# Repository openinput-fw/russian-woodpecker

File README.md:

# russian-woodpecker

*russian-woodpecker* is a usb HS (capable of 8kHz polling rate) 2.4GHz radio receiver dongle for use with input devices.

Please see the [documentation](https://russian-woodpecker.readthedocs.io/en/latest)
for more information.

## Specifications
- 8 kHz polling rate suppor
- 2.4GHz radio
- smol, but not that smol

## License

This hardware is licensed under the [CERN-OHL-P v2](LICENSE) license.

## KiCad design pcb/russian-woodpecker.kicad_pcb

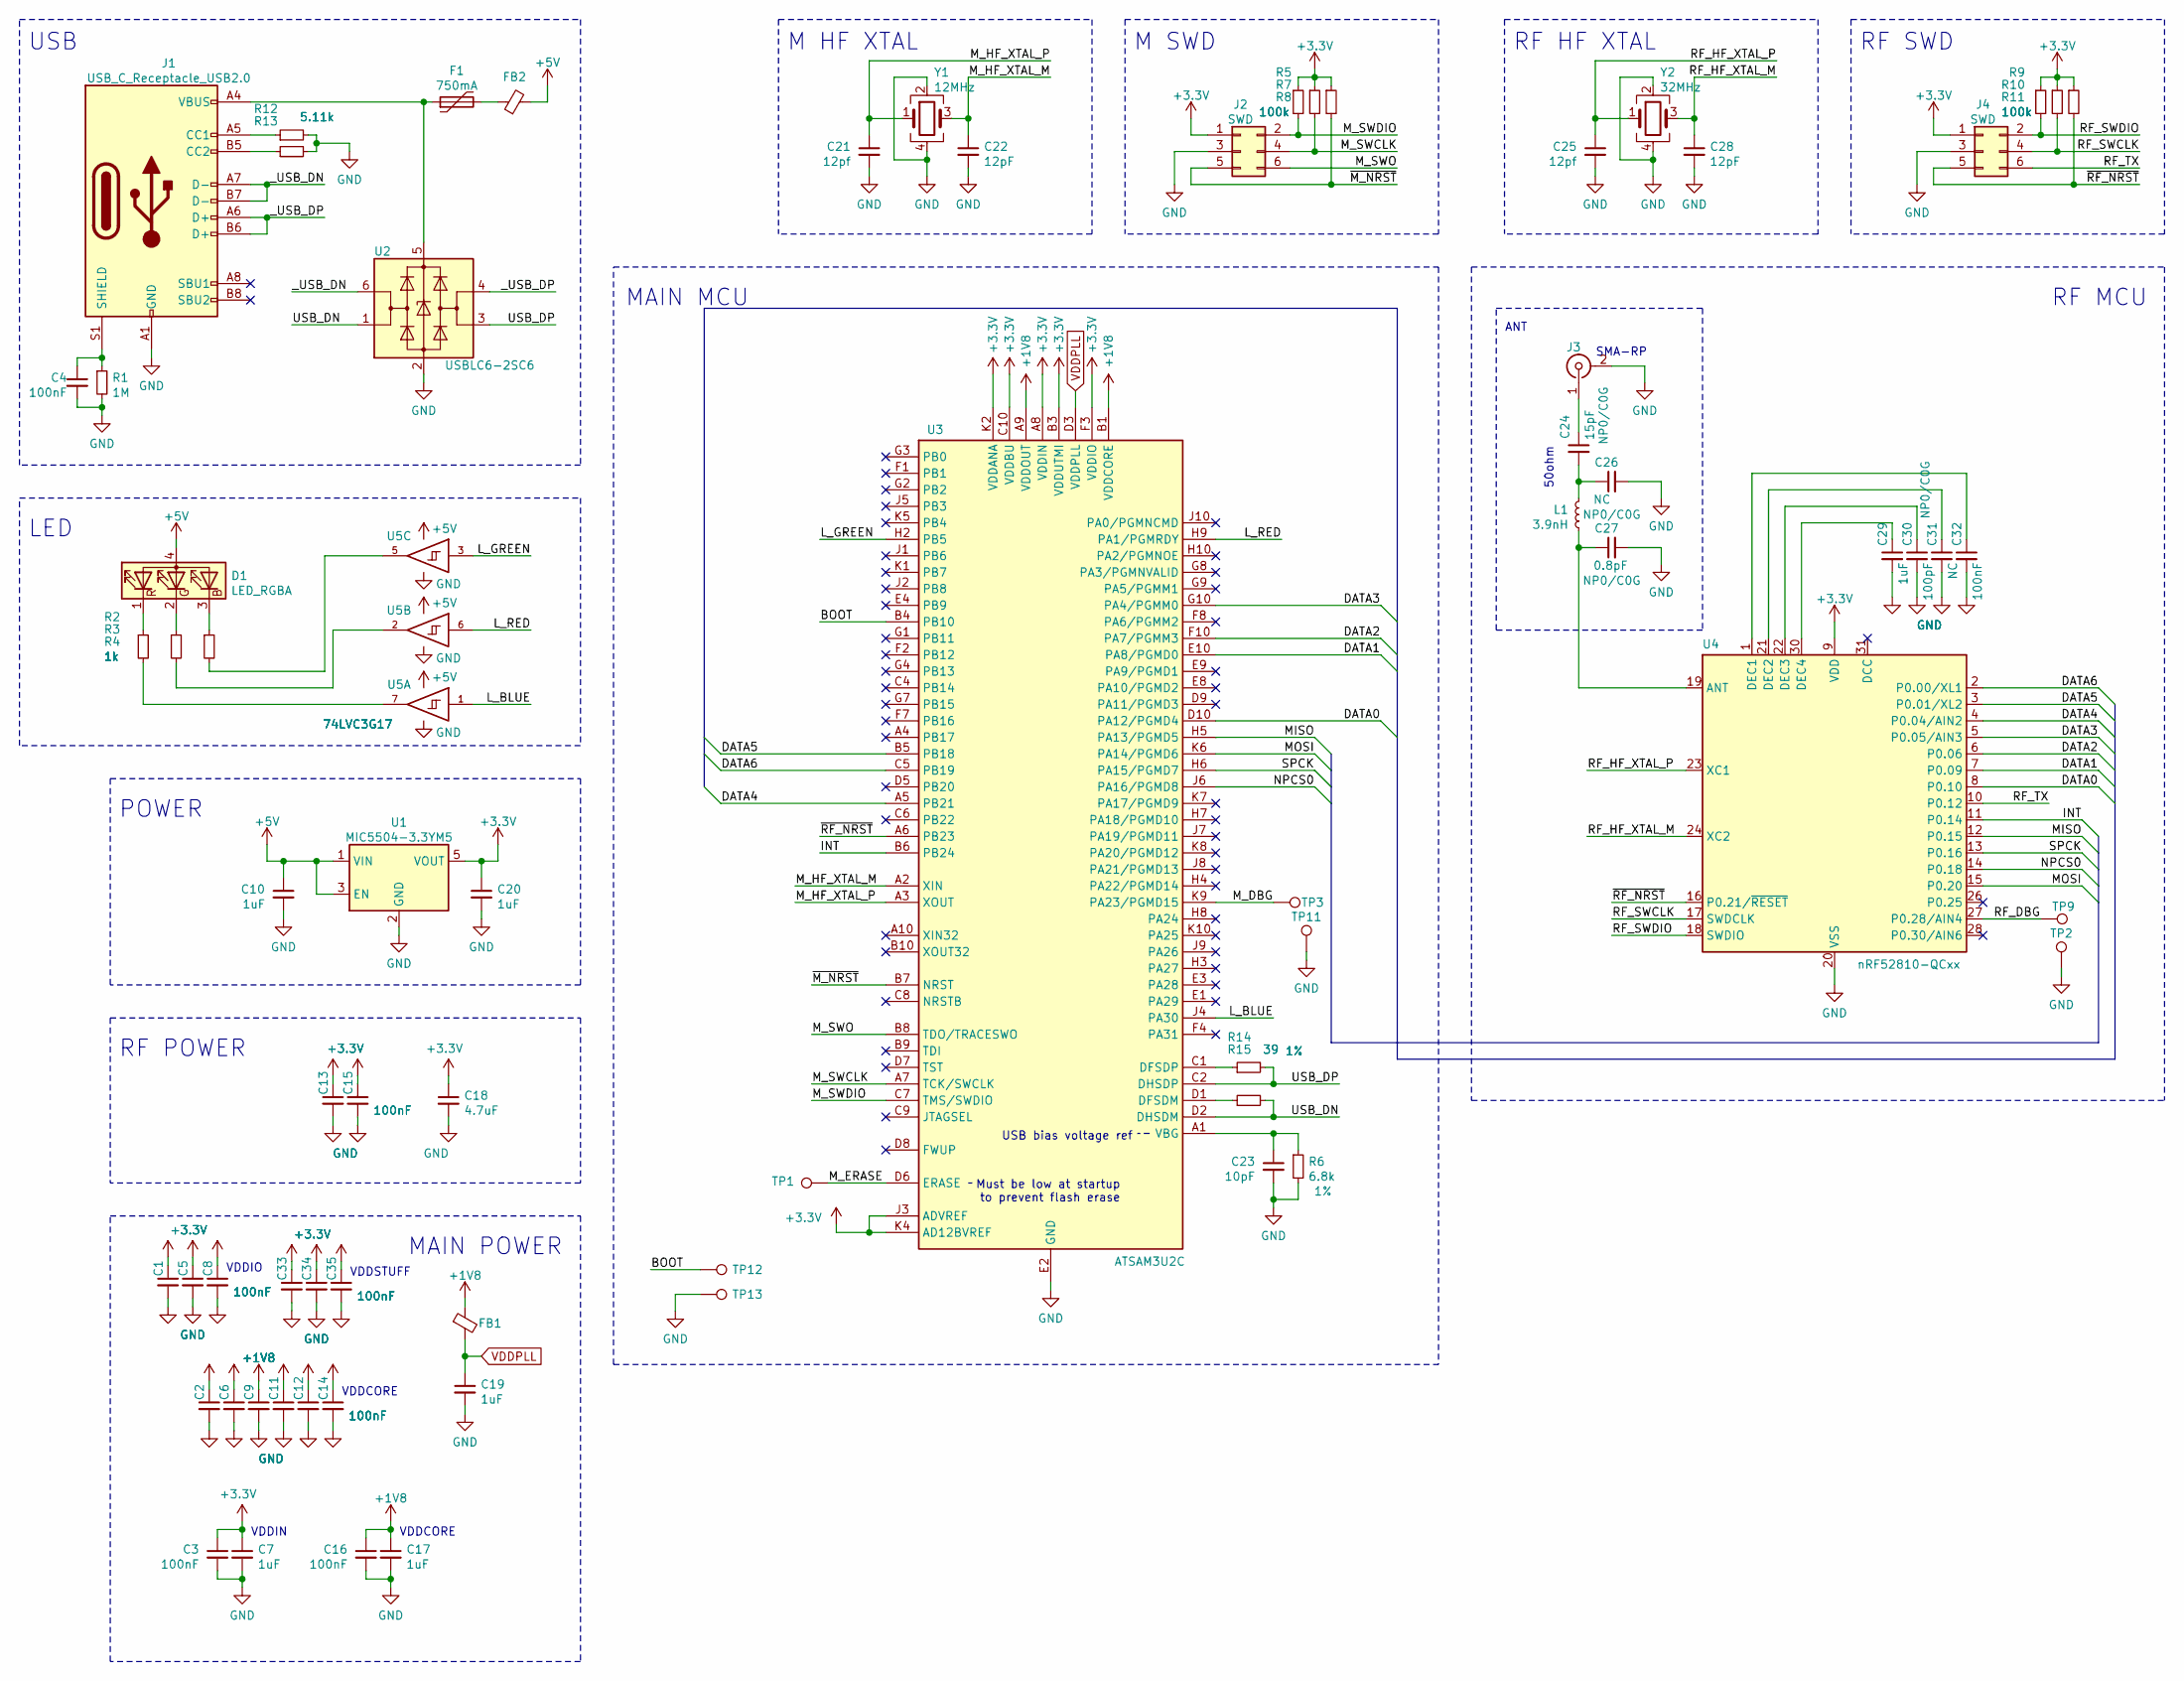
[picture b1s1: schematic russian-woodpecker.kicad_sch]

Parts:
C1, C2, C3, C4, C5, C6, C8, C9, C11, C12, C13, C14, C15, C16, C32, C33, C34, C35: 100nF; C_0402_1005Metric
C7, C10, C17, C19, C20, C29: 1uF; C_0402_1005Metric
C18: 4.7uF; C_0603_1608Metric
C21, C25: 12pf; C_0402_1005Metric
C22, C28: 12pF; C_0402_1005Metric
C23: 10pF; C_0402_1005Metric
C24: 15pF; C_0402_1005Metric
C26, C31: NC; C_0402_1005Metric
C27: 0.8pF; C_0402_1005Metric
C30: 100pF; C_0402_1005Metric
D1: LED_RGBA; LED_LiteOn_LTST-C19HE1WT
F1: 750mA; Fuse_0603_1608Metric
FB1, FB2: L_0402_1005Metric
J1: USB_C_Receptacle_USB2.0; USB_C_Receptacle_HRO_TYPE-C-31-M-12
J2, J4: SWD; Tag-Connect_TC2030-IDC-NL_2x03_P1.27mm_Vertical
J3: SMA-RP; SMA_Amphenol_132289_EdgeMount
L1: 3.9nH; L_0402_1005Metric
R1: 1M; R_0402_1005Metric
R2, R3, R4: 1k; R_0402_1005Metric
R5, R7, R8, R9, R10, R11: 100k; R_0402_1005Metric
R6: 6.8k; R_0402_1005Metric; Tolerance 1%
R12, R13: 5.11k; R_0402_1005Metric
R14, R15: 39; R_0402_1005Metric; Tolerance 1%
TP1, TP2, TP3, TP9, TP11, TP12, TP13: TestPoint_Pad_D1.0mm
U1: MIC5504-3.3YM5; SOT-23-5
U2: USBLC6-2SC6; SOT-23-6
U3: ATSAM3U2C; TFBGA-100_9.0x9.0mm_Layout10x10_P0.8mm
U4: nRF52810-QCxx; QFN-32-1EP_5x5mm_P0.5mm_EP3.6x3.6mm
U5: 74LVC3G17; VSSOP-8_2.3x2mm_P0.5mm
Y1: 12MHz; Crystal_SMD_3225-4Pin_3.2x2.5mm
Y2: 32MHz; Crystal_SMD_3225-4Pin_3.2x2.5mm

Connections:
+1V8: C2.1, C6.1, C9.1, C11.1, C12.1, C14.1, C16.1, C17.1, FB1.1, U3.A9 (VDDOUT), U3.B1 (VDDCORE), U3.D4 (VDDCORE), U3.E7 (VDDCORE), U3.F9 (VDDCORE), U3.G5 (VDDCORE), U3.H1 (VDDCORE)
+3V3: C1.1, C3.1, C5.1, C7.1, C8.1, C13.1, C15.1, C18.1, C20.1, C33.1, C34.1, C35.1, J2.1, J4.1, R5.1, R7.1, R8.1, R9.1, R10.1, R11.1, U1.5 (VOUT), U3.A8 (VDDIN), U3.B3 (VDDUTMI), U3.C10 (VDDBU), U3.E6 (VDDIO), U3.F3 (VDDIO), U3.F5 (VDDIO), U3.J3 (ADVREF), U3.K2 (VDDANA), U3.K4 (AD12BVREF), U4.9 (VDD), U4.25 (VDD), U4.32 (VDD)
+5V: C10.1, D1.4 (A), FB2.2, U1.1 (VIN), U1.3 (EN), U5.8 (VCC)
/BOOT: TP12.1, U3.B4 (PB10)
/DATA0: U3.D10 (PA12/PGMD4), U4.8 (P0.10)
/DATA1: U3.E10 (PA8/PGMD0), U4.7 (P0.09)
/DATA2: U3.F10 (PA7/PGMM3), U4.6 (P0.06)
/DATA3: U3.G10 (PA4/PGMM0), U4.5 (P0.05/AIN3)
/DATA4: U3.A5 (PB21), U4.4 (P0.04/AIN2)
/DATA5: U3.B5 (PB18), U4.3 (P0.01/XL2)
/DATA6: U3.C5 (PB19), U4.2 (P0.00/XL1)
/INT: U3.B6 (PB24), U4.11 (P0.14)
/L_BLUE: U3.J4 (PA30), U5.1
/L_GREEN: U3.H2 (PB5), U5.3
/L_RED: U3.H9 (PA1/PGMRDY), U5.6
/MISO: U3.H5 (PA13/PGMD5), U4.12 (P0.15)
/MOSI: U3.K6 (PA14/PGMD6), U4.15 (P0.20)
/M_DBG: TP3.1, U3.K9 (PA23/PGMD15)
/M_ERASE: TP1.1, U3.D6 (ERASE)
/M_HF_XTAL_M: C22.1, U3.A2 (XIN), Y1.3
/M_HF_XTAL_P: C21.1, U3.A3 (XOUT), Y1.1
/M_SWCLK: J2.4, R7.2, U3.A7 (TCK/SWCLK)
/M_SWDIO: J2.2, R5.2, U3.C7 (TMS/SWDIO)
/M_SWO: J2.6, U3.B8 (TDO/TRACESWO)
/NPCS0: U3.J6 (PA16/PGMD8), U4.14 (P0.18)
/RF_DBG: TP9.1, U4.27 (P0.28/AIN4)
/RF_HF_XTAL_M: C28.1, U4.24 (XC2), Y2.3
/RF_HF_XTAL_P: C25.1, U4.23 (XC1), Y2.1
/RF_SWCLK: J4.4, R10.2, U4.17 (SWDCLK)
/RF_SWDIO: J4.2, R9.2, U4.18 (SWDIO)
/RF_TX: J4.6, U4.10 (P0.12)
/SPCK: U3.H6 (PA15/PGMD7), U4.13 (P0.16)
/USB_DN: R15.2, U2.1 (I/O1), U3.D2 (DHSDM)
/USB_DP: R14.2, U2.3 (I/O2), U3.C2 (DHSDP)
/_USB_DN: J1.A7 (D-), J1.B7 (D-), U2.6 (I/O1)
/_USB_DP: J1.A6 (D+), J1.B6 (D+), U2.4 (I/O2)
/~M_NRST: J2.5, R8.2, U3.B7 (NRST)
/~RF_NRST: J4.5, R11.2, U3.A6 (PB23), U4.16 (P0.21/~RESET)
GND: C1.2, C2.2, C3.2, C4.2, C5.2, C6.2, C7.2, C8.2, C9.2, C10.2, C11.2, C12.2, C13.2, C14.2, C15.2, C16.2, C17.2, C18.2, C19.2, C20.2, C21.2, C22.2, C23.2, C25.2, C26.2, C27.2, C28.2, C29.2, C30.2, C31.2, C32.2, C33.2, C34.2, C35.2, J1.A1 (GND), J1.A12 (GND), J1.B1 (GND), J1.B12 (GND), J2.3, J3.2 (Ext), J4.3, R1.2, R6.2, R12.2, R13.2, TP2.1, TP11.1, TP13.1, U1.2 (GND), U2.2 (GND), U3.B2 (GNDUTMI), U3.C3 (GNDPLL), U3.E2 (GND), U3.E5 (GNDBU), U3.F6 (GND), U3.G6 (GND), U3.K3 (GNDANA), U4.20 (VSS), U4.29 (VSS), U4.33 (VSS), U5.4 (GND), Y1.2, Y1.4, Y2.2, Y2.4
unnamed: C4.1, J1.S1 (SHIELD), R1.1
unnamed: C23.1, R6.1, U3.A1 (VBG)
unnamed: C24.1, J3.1 (In)
unnamed: C24.2, C26.1, L1.2
unnamed: C27.1, L1.1, U4.19 (ANT)
unnamed: C29.1, U4.30 (DEC4)
unnamed: C30.1, U4.22 (DEC3)
unnamed: C31.1, U4.21 (DEC2)
unnamed: C32.1, U4.1 (DEC1)
unnamed: F1.1, J1.A4 (VBUS), J1.A9 (VBUS), J1.B4 (VBUS), J1.B9 (VBUS), U2.5 (VBUS)
unnamed: F1.2, FB2.1
unnamed: J1.A5 (CC1), R12.1
unnamed: J1.B5 (CC2), R13.1
unnamed: D1.1 (RK), R2.1
unnamed: R2.2, U5.7
unnamed: D1.2 (GK), R3.1
unnamed: R3.2, U5.2
unnamed: D1.3 (BK), R4.1
unnamed: R4.2, U5.5
unnamed: R14.1, U3.C1 (DFSDP)
unnamed: R15.1, U3.D1 (DFSDM)
VDDPLL: C19.1, FB1.2, U3.D3 (VDDPLL)

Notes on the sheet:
RF POWER
RF MCU
VDDIO
USB bias voltage ref
Must be low at startup to prevent flash erase
VDDCORE
USB
M SWD
RF HF XTAL
MAIN POWER
VDDSTUFF
VDDIN
RF SWD
LED
MAIN MCU
SMA-RP
M HF XTAL
POWER
ANT
50ohm

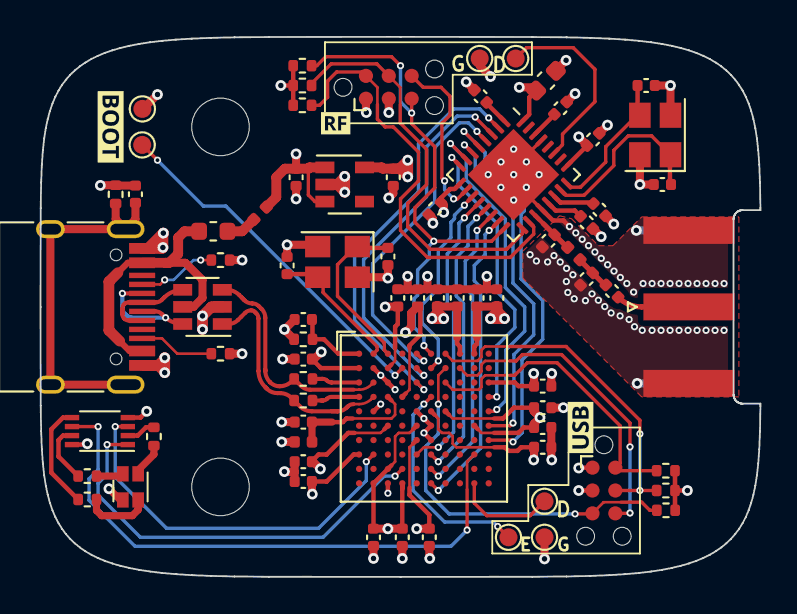
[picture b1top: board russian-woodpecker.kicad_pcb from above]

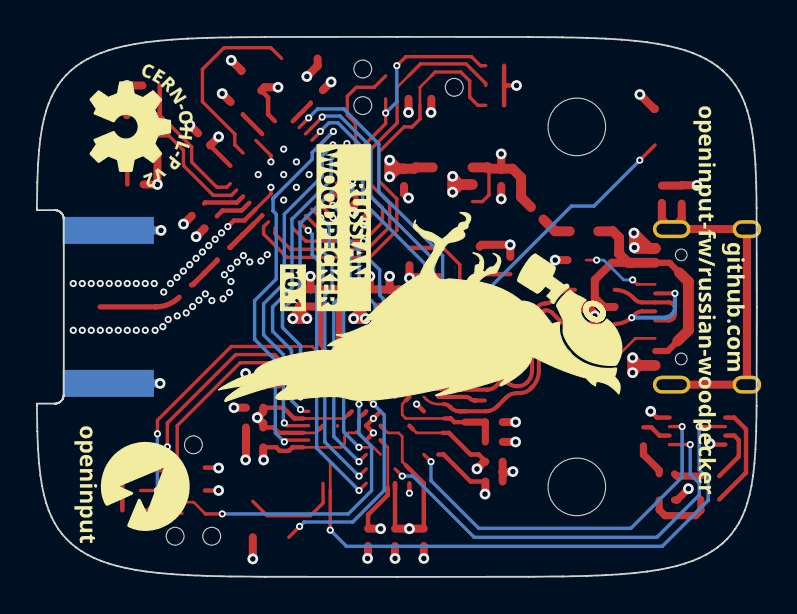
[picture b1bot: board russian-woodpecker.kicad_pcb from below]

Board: 4 copper layers, 40.0 x 30.0 mm, 82 parts (4 on the bottom side), 61 nets.

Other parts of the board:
MH0, MH0#2: MountingHole_3.2mm_M3
svg2mod, svg2mod#2, svg2mod#3, svg2mod#4, svg2mod#5, svg2mod#6, svg2mod#7: G***; svg2mod

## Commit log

2021-05-25 kicad: create kicad project
2021-05-26 kicad: add atsam3u lib
2021-05-26 sch: rev 0.1
2021-05-29 kicad: add SMA connector models
2021-05-29 cad: add dxf outline (superellipsoid genned in openscad)
2021-05-29 gitignore: kicad: add bakup entry in gitignore
2021-05-29 pcb: add boot button, change usb to type C, initial board
2021-05-29 readme: add board view
2021-05-29 asset: add woodpecker 'logo'
2021-06-05 pcb: finalize routing
2021-06-08 repo: update references in preparation for transfer to openinput org
2021-06-08 pcbnew: fix 3d model references
2021-06-08 readme: add oi logo, update board view
2021-06-08 assets: remove unused board view for r0.0
2021-06-08 kicad pro: update drc preferences
2021-06-09 pcb: change led drive circuitry
2021-10-15 assets: oi logo cleanup
2021-11-22 assets: move assets inside docs
2021-11-22 docs: add initial readthedocs documentation
2021-11-22 readme: remove documentation that is now on readthedocs
2021-11-22 docs: update index
2021-11-22 docs: move firmware info from readme to docs
2021-11-23 docs: add link to source
2021-12-15 readme: formating
2022-01-07 kicad: save pcb with v6.0

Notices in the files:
pcb/russian-woodpecker.kicad_pcb:
This source describes Open Hardware and is licensed under the CERN-OHL-Pv2
Copyright (c) Rafael Silva
